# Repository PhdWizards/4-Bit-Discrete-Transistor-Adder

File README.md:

# 4-Bit Transistor Adder
A fully functional **4-bit binary adder** built using discrete transistor-resistor logic and standard 74HC-series logic ICs.
The project was developed from the initial logic design and transistor-level simulation to a custom two-layer PCB, PCB manufacturing, component assembly, and hardware testing.
The final circuit accepts two 4-bit binary numbers, adds them together, converts the resulting 5-bit value into decimal digits, and displays the result on two 7-segment displays.

## Overview
The main goal of this project was to design and build a physical digital calculator without relying on a microcontroller for the main arithmetic logic.
The core 4-bit adder was developed using **discrete transistor-resistor logic**.
The project includes:
- 4-bit binary addition
- Discrete transistor-based logic
- 5-bit binary result
- Binary-to-BCD conversion
- Two 7-segment displays
- CD4511 BCD-to-7-segment drivers
- Manual binary input using switches
- LED indicators for the binary result
- Custom two-layer PCB
- Complete KiCad schematic
- PCB design and Gerber manufacturing files
- Interactive Bill of Materials
- Falstad and Tinkercad simulations

## Specifications
| Parameter | Value |
|-----------|-------|
| Operation | 4-bit + 4-bit binary addition |
| Input A | 4 bits |
| Input B | 4 bits |
| Result | 5 bits |
| Result range | 0–30 |
| Supply voltage | 5 V |
| Power input | USB-C |
| PCB | 2-layer |
| PCB size | 166.37 × 181.61 mm |
| Main transistor | BC337-25 |
| Transistors | 100 |
| Resistors | 178 |
| 7-segment displays | 2 |
| BCD drivers | 2 × CD4511 |
| Binary input switches | 8 |
| LEDs | 6 |
| Microcontroller | None |

## How It Works

Two 4-bit binary values are entered using eight switches:
```text
A3 A2 A1 A0
B3 B2 B1 B0
```
The values are added together by the transistor-based logic, producing a 5-bit result:
```text
S4 S3 S2 S1 S0
```
The maximum possible result is:
```text
1111₂ + 1111₂ = 11110₂
```
which corresponds to:
```text
30₁₀
```
The 5-bit result is then converted into BCD:
```text
        5-bit Binary Result
                  │
                  ▼
          Binary-to-BCD
           Conversion
                  │
          ┌───────┴───────┐
          ▼               ▼
      Tens BCD         Ones BCD
          │               │
          ▼               ▼
       CD4511           CD4511
          │               │
          ▼               ▼
      7-Segment        7-Segment
       Display           Display
```
For example:
```text
10101₂ = 21₁₀
```
The two displays therefore show:
```text
21
```

## Hardware

### Final Board

## PCB Design

The PCB was designed in **KiCad** as a two-layer board.

### Front Side

### Back Side

### All Copper Layers

### 3D Model

## Schematic
The complete schematic was designed in KiCad and contains the transistor-based adder, logic ICs, BCD conversion, display drivers, inputs, indicators, and power circuitry.

A PDF version of the schematic is included in the `schematic` directory.
[**Open Schematic PDF**](schematic/sch.pdf)

## Bill of Materials

An **Interactive BOM** generated from KiCad is included in the repository.
It provides:
- Component references
- Component values
- Footprints
- Quantities
- Front and back PCB views
- Component locations
[**Open Interactive BOM**](bom/calculator-BOM.html)

## Simulation

Simulation was an important part of the development process.
Two different simulation environments were used for different stages of the project.

### Falstad
Falstad was used to learn and develop the transistor-based logic from the ground up.
The 4-bit adder was built step by step, starting from transistor-level digital logic and gradually combining the individual stages into a complete working 4-bit adder.
A downloadable Falstad simulation file is also included in the repository.
[**Open Simulation Documentation**](simulation/README.md)

### Tinkercad
Tinkercad was used to verify the digital logic and binary-to-BCD conversion.
The interactive Tinkercad simulation can be accessed through the simulation documentation.

## Development Process

The project was developed through the following stages:
```text
Concept
   ↓
Logic Design
   ↓
Transistor-Level Development
   ↓
Falstad Simulation
   ↓
Working 4-Bit Adder
   ↓
Tinkercad Simulation
   ↓
KiCad Schematic
   ↓
PCB Layout
   ↓
PCB Manufacturing
   ↓
Component Assembly
   ↓
Hardware Testing
```
The purpose of this workflow was to validate the logic progressively before moving to the final physical implementation.

## Manufacturing Files

The repository contains the files required to reproduce the PCB.
The `pcb` directory includes:
- KiCad PCB files
- Gerber manufacturing files
The schematic directory contains the KiCad schematic and PDF documentation.

## Repository Structure
```text
4-Bit-Transistor-Adder/
│
├── 📁 bom/
│   └── Interactive BOM
│
├── 📁 images/
│   ├── Project photos
│   ├── PCB renders
│   ├── PCB layers
│   ├── Schematic images
│   └── Simulation screenshots
│
├── 📁 pcb/
│   ├── KiCad PCB files
│   └── Gerber files
│
├── 📁 schematic/
│   ├── KiCad schematic
│   └── Schematic PDF
│
├── 📁 simulation/
│   ├── README.md
│   └── Falstad simulation file
│
└── README.md
```

# Tools Used
- **KiCad** — schematic and PCB design
- **Falstad Circuit Simulator** — transistor-level logic development
- **Tinkercad Circuits** — digital logic simulation

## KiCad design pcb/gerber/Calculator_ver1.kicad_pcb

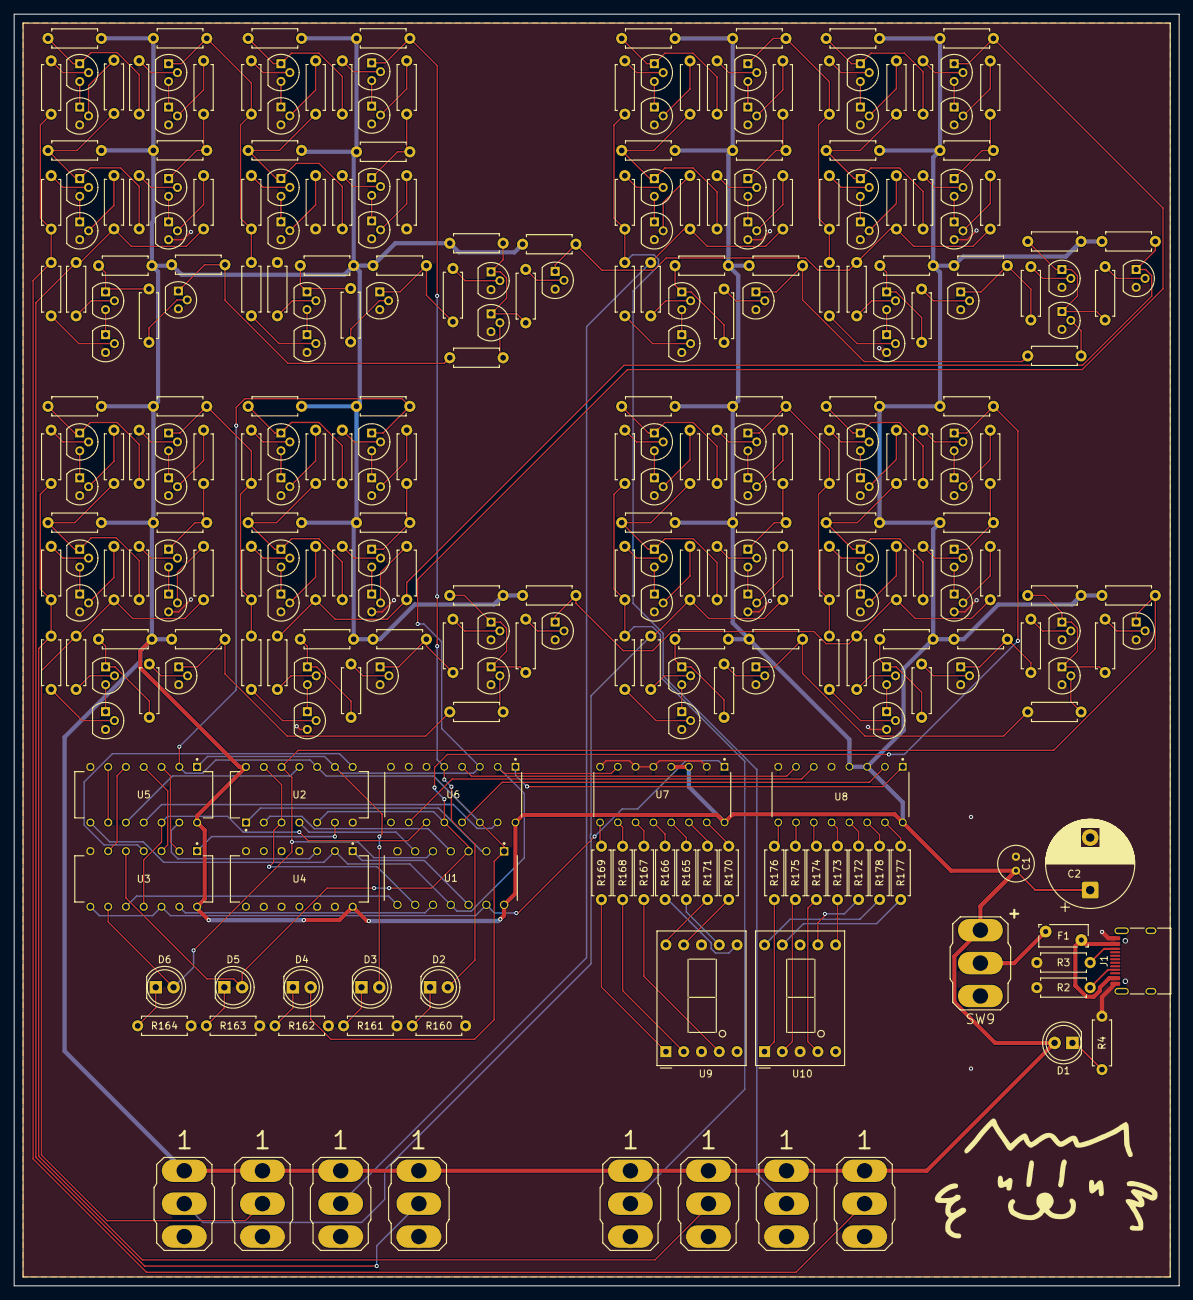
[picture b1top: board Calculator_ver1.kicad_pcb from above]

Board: 2 copper layers, 166.4 x 181.6 mm, 308 parts (0 on the bottom side), 267 nets.

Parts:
C1: 100nF; C_Radial_D5.0mm_H5.0mm_P2.00mm
C2: 100uF; CP_Radial_D12.5mm_P7.50mm
D1, D2, D3, D4, D5, D6: LED; LED_D5.0mm
F1: MF-R075; Fuse_Bourns_MF-RHT070
J1: USB_C_Receptacle_PowerOnly_24P; USB_C_Receptacle_HRO_TYPE-C-31-M-12
Q1, Q2, Q3, Q4, Q5, Q6, Q7, Q8, Q9, Q10, Q11, Q12, Q13, Q14, Q15, Q16, Q17, Q18, Q19, Q20, Q21, Q22, Q23, Q24, Q25, Q26, Q27, Q28, Q29, Q30, Q31, Q32, Q33, Q34, Q35, Q36, Q37, Q38, Q39, Q40, Q41, Q42, Q43, Q44, Q45, Q46, Q47, Q48, Q49, Q50, Q51, Q52, Q53, Q54, Q55, Q56, Q57, Q58, Q59, Q60, Q61, Q62, Q63, Q64, Q65, Q66, Q67, Q68, Q69, Q70, Q71, Q72, Q73, Q74, Q75, Q76, Q77, Q78, Q79, Q80, Q81, Q82, Q83, Q84, Q85, Q86, Q87, Q88, Q89, Q90, Q91, Q92, Q93, Q94, Q95, Q96, Q97, Q98, Q99, Q100: NPN; TO-92
R1, R5, R6, R7, R8, R9, R10, R11, R12, R13, R14, R15, R16, R17, R18, R19, R20, R21, R22, R23, R24, R25, R26, R27, R28, R29, R30, R31, R32, R33, R34, R35, R36, R37, R38, R39, R40, R41, R42, R43, R44, R45, R46, R47, R48, R49, R50, R51, R52, R53, R54, R55, R56, R57, R58, R59, R60, R61, R62, R63, R64, R65, R66, R67, R68, R69, R70, R71, R72, R73, R74, R75, R76, R77, R78, R79, R80, R81, R82, R83, R84, R85, R86, R87, R88, R89, R90, R91, R92, R93, R94, R95, R96, R97, R98, R99, R100, R101, R102, R103, R104, R105, R106, R107, R108, R109, R110, R111, R112, R113, R114, R115, R116, R117, R118, R119, R120, R121, R122, R123, R124, R125, R126, R127, R128, R129, R130, R131, R132, R133, R134, R135, R136, R137, R138, R139, R140, R141, R142, R143, R144, R145, R146, R147, R148, R149, R150, R151, R152, R153, R154, R155, R156, R157, R158, R159: 1k; R_Axial_DIN0207_L6.3mm_D2.5mm_P7.62mm_Horizontal
R2, R3: 5.1k; R_Axial_DIN0207_L6.3mm_D2.5mm_P7.62mm_Horizontal
R4, R160, R161, R162, R163, R164: 330R; R_Axial_DIN0207_L6.3mm_D2.5mm_P7.62mm_Horizontal
R165, R166, R167, R168, R169, R170, R171, R172, R173, R174, R175, R176, R177, R178: 330; R_Axial_DIN0207_L6.3mm_D2.5mm_P7.62mm_Horizontal
SW1, SW2, SW3, SW4, SW5, SW6, SW7, SW8, SW9: MTS-102
U1: 74HC04N; DIP764W47P254L1920H431Q14
U2, U3, U4: SN74HC08N; DIP794W45P254L1969H508Q14
U5: SN74HC32N; DIP794W45P254L1969H508Q14
U6: CD74HC283E; DIP794W45P254L1969H508Q16
U7, U8: CD4511BE; DIP794W45P254L1969H508Q16
U9, U10: D148K; D1X8K
g: LOGO; logocat

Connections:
+5V: C1.1, C2.1, D1.2 (A), R5.2, R9.2, R12.2, R15.2, R18.2, R20.2, R23.2, R30.2, R31.2, R32.2, R36.2, R37.2, R39.2, R42.2, R45.2, R52.2, R53.2, R54.2, R58.2, R59.2, R62.2, R69.2, R70.2, R71.2, R77.2, R78.2, R79.2, R81.2, R84.2, R91.2, R92.2, R93.2, R97.2, R98.2, R101.2, R108.2, R109.2, R110.2, R116.2, R117.2, R118.2, R120.2, R123.2, R130.2, R131.2, R132.2, R136.2, R137.2, R140.2, R147.2, R148.2, R149.2, R155.2, R156.2, R157.2, R159.2, SW1.1 (A), SW2.1 (A), SW3.1 (A), SW4.1 (A), SW5.1 (A), SW6.1 (A), SW7.1 (A), SW8.1 (A), SW9.1 (A), U1.14 (VCC), U2.14 (VCC), U3.14 (VCC), U4.14 (VCC), U5.14 (VCC), U6.16 (VCC), U7.3 (~LT), U7.4 (~BL), U7.16 (VDD), U8.3 (~LT), U8.4 (~BL), U8.16 (VDD)
/A0: R1.1, R7.1, R17.1, SW1.2 (B)
/A1: R43.1, R46.1, R51.1, SW2.2 (B)
/A1I: U1.8 (4Y), U3.10 (3B)
/A2: R82.1, R85.1, R90.1, SW3.2 (B)
/A3: R121.1, R124.1, R129.1, SW4.2 (B)
/A11: U1.9 (4A), U2.3 (1Y), U2.13 (4B)
/A22: U2.6 (2Y), U3.1 (1A)
/A33: U2.8 (3Y), U3.4 (2A)
/A44: U2.11 (4Y), U5.10 (3B)
/B0: R6.1, R11.1, R16.1, SW5.2 (B)
/B1: R44.1, R49.1, R50.1, SW6.2 (B)
/B2: R83.1, R88.1, R89.1, SW7.2 (B)
/B3: R122.1, R127.1, R128.1, SW8.2 (B)
/B3I: U1.12 (6Y), U4.1 (1A)
/B11: U3.3 (1Y), U5.4 (2A)
/B22: U3.6 (2Y), U5.5 (2B)
/B33: U1.13 (6A), U3.8 (3Y), U3.12 (4A), U7.1 (B_IN)
/B44: U3.11 (4Y), U5.12 (4A), U6.11 (B3)
/C1: U4.3 (1Y), U5.13 (4B)
/Cout1: Q25.1 (C), R42.1, R61.1, R66.1, R67.1
/Cout2: Q50.1 (C), R81.1, R100.1, R105.1, R106.1
/Cout3: Q75.1 (C), R120.1, R139.1, R144.1, R145.1
/Cout4: D6.2 (A), Q100.1 (C), R159.1, U1.5 (3A), U2.12 (4A), U3.9 (3A)
/Cout4I: U1.6 (3Y), U2.4 (2A)
/D1: U3.2 (1B), U5.3 (1Y)
/D2: U5.6 (2Y), U5.9 (3A)
/D3: U1.11 (5A), U4.2 (1B), U5.8 (3Y), U6.2 (B1), U7.7 (A_IN)
/D3I: U1.10 (5Y), U3.13 (4B)
/D4: U5.11 (4Y), U6.15 (B2)
/S0: U6.4 (S0), U8.7 (A_IN)
/S1: U6.1 (S1), U8.1 (B_IN)
/S2: U6.13 (S2), U8.2 (C_IN)
/S3: U6.10 (S3), U8.6 (D_IN)
/Sum1: D2.2 (A), Q21.1 (C), R37.1, U6.5 (A0)
/Sum2: D3.2 (A), Q48.1 (C), R79.1, U2.9 (3A), U5.1 (1A), U6.3 (A1)
/Sum3: D4.2 (A), Q73.1 (C), R118.1, U1.1 (1A), U2.10 (3B), U5.2 (1B), U6.14 (A2)
/Sum3I: U1.2 (1Y), U2.1 (1A)
/Sum4: D5.2 (A), Q98.1 (C), R157.1, U1.3 (2A), U2.5 (2B), U3.5 (2B), U6.12 (A3)
/Sum4I: U1.4 (2Y), U2.2 (1B)
/VBUS: F1.1, J1.A4 (VBUS), J1.A9 (VBUS), J1.B4 (VBUS), J1.B9 (VBUS)
GND: C1.2, C2.2, J1.A1 (GND), J1.A12 (GND), J1.B1 (GND), J1.B12 (GND), Q2.3 (E), Q4.3 (E), Q6.3 (E), Q8.3 (E), Q10.3 (E), Q11.3 (E), Q13.3 (E), Q15.3 (E), Q17.3 (E), Q19.3 (E), Q20.3 (E), Q22.3 (E), Q23.3 (E), Q24.3 (E), Q25.3 (E), Q27.3 (E), Q29.3 (E), Q31.3 (E), Q33.3 (E), Q34.3 (E), Q36.3 (E), Q38.3 (E), Q40.3 (E), Q42.3 (E), Q44.3 (E), Q45.3 (E), Q46.3 (E), Q47.3 (E), Q49.3 (E), Q50.3 (E), Q52.3 (E), Q54.3 (E), Q56.3 (E), Q58.3 (E), Q59.3 (E), Q61.3 (E), Q63.3 (E), Q65.3 (E), Q67.3 (E), Q69.3 (E), Q70.3 (E), Q71.3 (E), Q72.3 (E), Q74.3 (E), Q75.3 (E), Q77.3 (E), Q79.3 (E), Q81.3 (E), Q83.3 (E), Q84.3 (E), Q86.3 (E), Q88.3 (E), Q90.3 (E), Q92.3 (E), Q94.3 (E), Q95.3 (E), Q96.3 (E), Q97.3 (E), Q99.3 (E), Q100.3 (E), R2.2, R3.2, R4.2, R22.1, R27.1, R28.1, R160.2, R161.2, R162.2, R163.2, R164.2, SW1.3 (C), SW2.3 (C), SW3.3 (C), SW4.3 (C), SW5.3 (C), SW6.3 (C), SW7.3 (C), SW8.3 (C), U1.7 (GND), U2.7 (GND), U3.7 (GND), U4.4 (2A), U4.5 (2B), U4.7 (GND), U4.9 (3A), U4.10 (3B), U4.12 (4A), U4.13 (4B), U5.7 (GND), U6.6 (B0), U6.7 (CIN), U6.8 (GND), U7.2 (C_IN), U7.5 (LE/~STROBE), U7.6 (D_IN), U7.8 (VSS), U8.5 (LE/~STROBE), U8.8 (VSS), U9.3 (CC), U9.8 (CC), U10.3 (CC), U10.8 (CC)
unnamed: D1.1 (K), R4.1
unnamed: D2.1 (K), R160.1
unnamed: D3.1 (K), R161.1
unnamed: D4.1 (K), R162.1
unnamed: D5.1 (K), R163.1
unnamed: D6.1 (K), R164.1
unnamed: J1.A5 (CC1), R2.1
unnamed: J1.B5 (CC2), R3.1
unnamed: Q1.2 (B), R1.2
unnamed: Q1.1 (C), R5.1, R8.1, R10.1
unnamed: Q1.3 (E), Q2.1 (C)
unnamed: Q2.2 (B), R6.2
unnamed: Q3.2 (B), R7.2
unnamed: Q3.1 (C), R9.1, R13.1
unnamed: Q3.3 (E), Q4.1 (C)
unnamed: Q4.2 (B), R8.2
unnamed: Q5.2 (B), R10.2
unnamed: Q5.1 (C), R12.1, R14.1
unnamed: Q5.3 (E), Q6.1 (C)
unnamed: Q6.2 (B), R11.2
unnamed: Q7.2 (B), R13.2
unnamed: Q7.1 (C), R15.1, R21.1, R24.1, R29.1
unnamed: Q7.3 (E), Q8.1 (C)
unnamed: Q8.2 (B), R14.2
unnamed: Q9.2 (B), R16.2
unnamed: Q9.1 (C), R18.1, R19.1
unnamed: Q10.2 (B), R17.2
unnamed: Q9.3 (E), Q10.1 (C)
unnamed: Q11.2 (B), R19.2
unnamed: Q11.1 (C), R20.1, R40.1
unnamed: Q12.2 (B), R21.2
unnamed: Q12.1 (C), R23.1, R25.1, R26.1
unnamed: Q12.3 (E), Q13.1 (C)
unnamed: Q13.2 (B), R22.2
unnamed: Q14.2 (B), R24.2
unnamed: Q14.1 (C), R30.1, R34.1
unnamed: Q14.3 (E), Q15.1 (C)
unnamed: Q15.2 (B), R25.2
unnamed: Q16.2 (B), R26.2
unnamed: Q16.1 (C), R31.1, R35.1
unnamed: Q16.3 (E), Q17.1 (C)
unnamed: Q17.2 (B), R27.2
unnamed: Q18.2 (B), R28.2
unnamed: Q18.1 (C), R32.1, R33.1
unnamed: Q18.3 (E), Q19.1 (C)
unnamed: Q19.2 (B), R29.2
unnamed: Q20.2 (B), R33.2
unnamed: Q20.1 (C), R36.1, R38.1
unnamed: Q21.2 (B), R34.2
unnamed: Q21.3 (E), Q22.1 (C)
unnamed: Q22.2 (B), R35.2
unnamed: Q23.2 (B), R38.2
unnamed: Q23.1 (C), Q24.1 (C), R39.1, R41.1
unnamed: Q24.2 (B), R40.2
unnamed: Q25.2 (B), R41.2
unnamed: Q26.2 (B), R43.2
unnamed: Q26.1 (C), R45.1, R47.1, R48.1
unnamed: Q26.3 (E), Q27.1 (C)
unnamed: Q27.2 (B), R44.2
unnamed: Q28.2 (B), R46.2
unnamed: Q28.1 (C), R52.1, R56.1
unnamed: Q28.3 (E), Q29.1 (C)
unnamed: Q29.2 (B), R47.2
unnamed: Q30.2 (B), R48.2
unnamed: Q30.1 (C), R53.1, R57.1
unnamed: Q30.3 (E), Q31.1 (C)
unnamed: Q31.2 (B), R49.2
unnamed: Q32.2 (B), R50.2
unnamed: Q32.1 (C), R54.1, R55.1
unnamed: Q32.3 (E), Q33.1 (C)
unnamed: Q33.2 (B), R51.2
unnamed: Q34.2 (B), R55.2
unnamed: Q34.1 (C), R58.1, R74.1
unnamed: Q35.2 (B), R56.2
unnamed: Q35.1 (C), R59.1, R60.1, R63.1, R68.1
unnamed: Q35.3 (E), Q36.1 (C)
unnamed: Q36.2 (B), R57.2
unnamed: Q37.2 (B), R60.2
unnamed: Q37.1 (C), R62.1, R64.1, R65.1
unnamed: Q37.3 (E), Q38.1 (C)
unnamed: Q38.2 (B), R61.2
unnamed: Q39.2 (B), R63.2
unnamed: Q39.1 (C), R69.1, R75.1
unnamed: Q39.3 (E), Q40.1 (C)
unnamed: Q40.2 (B), R64.2
unnamed: Q41.2 (B), R65.2
unnamed: Q41.1 (C), R70.1, R76.1
unnamed: Q41.3 (E), Q42.1 (C)
unnamed: Q42.2 (B), R66.2
unnamed: Q43.2 (B), R67.2
unnamed: Q43.1 (C), R71.1, R72.1
unnamed: Q43.3 (E), Q44.1 (C)
unnamed: Q44.2 (B), R68.2
unnamed: Q45.2 (B), R72.2
unnamed: Q45.1 (C), R73.1, R77.1
unnamed: Q46.2 (B), R73.2
unnamed: Q46.1 (C), Q47.1 (C), R78.1, R80.1
unnamed: Q47.2 (B), R74.2
unnamed: Q48.2 (B), R75.2
unnamed: Q48.3 (E), Q49.1 (C)
unnamed: Q49.2 (B), R76.2
unnamed: Q50.2 (B), R80.2
unnamed: Q51.2 (B), R82.2
unnamed: Q51.1 (C), R84.1, R86.1, R87.1
unnamed: Q51.3 (E), Q52.1 (C)
unnamed: Q52.2 (B), R83.2
unnamed: Q53.2 (B), R85.2
unnamed: Q53.1 (C), R91.1, R95.1
unnamed: Q53.3 (E), Q54.1 (C)
unnamed: Q54.2 (B), R86.2
unnamed: Q55.2 (B), R87.2
unnamed: Q55.1 (C), R92.1, R96.1
unnamed: Q55.3 (E), Q56.1 (C)
unnamed: Q56.2 (B), R88.2
unnamed: Q57.2 (B), R89.2
unnamed: Q57.1 (C), R93.1, R94.1
unnamed: Q57.3 (E), Q58.1 (C)
unnamed: Q58.2 (B), R90.2
unnamed: Q59.2 (B), R94.2
unnamed: Q59.1 (C), R97.1, R113.1
unnamed: Q60.2 (B), R95.2
unnamed: Q60.1 (C), R98.1, R99.1, R102.1, R107.1
unnamed: Q60.3 (E), Q61.1 (C)
unnamed: Q61.2 (B), R96.2
unnamed: Q62.2 (B), R99.2
unnamed: Q62.1 (C), R101.1, R103.1, R104.1
unnamed: Q62.3 (E), Q63.1 (C)
unnamed: Q63.2 (B), R100.2
unnamed: Q64.2 (B), R102.2
unnamed: Q64.1 (C), R108.1, R114.1
unnamed: Q64.3 (E), Q65.1 (C)
unnamed: Q65.2 (B), R103.2
unnamed: Q66.2 (B), R104.2
unnamed: Q66.1 (C), R109.1, R115.1
unnamed: Q66.3 (E), Q67.1 (C)
unnamed: Q67.2 (B), R105.2
unnamed: Q68.2 (B), R106.2
unnamed: Q68.1 (C), R110.1, R111.1
unnamed: Q68.3 (E), Q69.1 (C)
unnamed: Q69.2 (B), R107.2
unnamed: Q70.2 (B), R111.2
unnamed: Q70.1 (C), R112.1, R116.1
unnamed: Q71.2 (B), R112.2
unnamed: Q71.1 (C), Q72.1 (C), R117.1, R119.1
unnamed: Q72.2 (B), R113.2
unnamed: Q73.2 (B), R114.2
unnamed: Q73.3 (E), Q74.1 (C)
unnamed: Q74.2 (B), R115.2
unnamed: Q75.2 (B), R119.2
unnamed: Q76.2 (B), R121.2
unnamed: Q76.1 (C), R123.1, R125.1, R126.1
unnamed: Q76.3 (E), Q77.1 (C)
unnamed: Q77.2 (B), R122.2
unnamed: Q78.2 (B), R124.2
unnamed: Q78.1 (C), R130.1, R134.1
unnamed: Q78.3 (E), Q79.1 (C)
unnamed: Q79.2 (B), R125.2
unnamed: Q80.2 (B), R126.2
unnamed: Q80.1 (C), R131.1, R135.1
unnamed: Q80.3 (E), Q81.1 (C)
unnamed: Q81.2 (B), R127.2
unnamed: Q82.2 (B), R128.2
unnamed: Q82.1 (C), R132.1, R133.1
unnamed: Q82.3 (E), Q83.1 (C)
unnamed: Q83.2 (B), R129.2
unnamed: Q84.2 (B), R133.2
unnamed: Q84.1 (C), R136.1, R152.1
unnamed: Q85.2 (B), R134.2
unnamed: Q85.1 (C), R137.1, R138.1, R141.1, R146.1
unnamed: Q85.3 (E), Q86.1 (C)
unnamed: Q86.2 (B), R135.2
unnamed: Q87.2 (B), R138.2
unnamed: Q87.1 (C), R140.1, R142.1, R143.1
unnamed: Q87.3 (E), Q88.1 (C)
unnamed: Q88.2 (B), R139.2
unnamed: Q89.2 (B), R141.2
unnamed: Q89.1 (C), R147.1, R153.1
unnamed: Q89.3 (E), Q90.1 (C)
unnamed: Q90.2 (B), R142.2
unnamed: Q91.2 (B), R143.2
unnamed: Q91.1 (C), R148.1, R154.1
unnamed: Q91.3 (E), Q92.1 (C)
unnamed: Q92.2 (B), R144.2
unnamed: Q93.2 (B), R145.2
unnamed: Q93.1 (C), R149.1, R150.1
unnamed: Q93.3 (E), Q94.1 (C)
unnamed: Q94.2 (B), R146.2
unnamed: Q95.2 (B), R150.2
unnamed: Q95.1 (C), R151.1, R155.1
unnamed: Q96.2 (B), R151.2
unnamed: Q96.1 (C), Q97.1 (C), R156.1, R158.1
unnamed: Q97.2 (B), R152.2
unnamed: Q98.2 (B), R153.2
unnamed: Q98.3 (E), Q99.1 (C)
unnamed: Q99.2 (B), R154.2
unnamed: Q100.2 (B), R158.2
unnamed: F1.2, SW9.2 (B)
unnamed: R165.2, U7.13 (A_OUT)
unnamed: R166.2, U7.12 (B_OUT)
unnamed: R167.2, U7.11 (C_OUT)
unnamed: R168.2, U7.10 (D_OUT)
unnamed: R169.2, U7.9 (E_OUT)
unnamed: R170.2, U7.15 (F_OUT)
unnamed: R171.2, U7.14 (G_OUT)
unnamed: R172.2, U8.13 (A_OUT)
unnamed: R173.2, U8.12 (B_OUT)
unnamed: R174.2, U8.11 (C_OUT)
unnamed: R175.2, U8.10 (D_OUT)
unnamed: R176.2, U8.9 (E_OUT)
unnamed: R177.2, U8.15 (F_OUT)
unnamed: R178.2, U8.14 (G_OUT)
unnamed: R165.1, U9.7 (A)
unnamed: R166.1, U9.6 (B)
unnamed: R167.1, U9.4 (C)
unnamed: R168.1, U9.2 (D)
unnamed: R169.1, U9.1 (E)
unnamed: R170.1, U9.9 (F)
unnamed: R171.1, U9.10 (G)
unnamed: R172.1, U10.7 (A)
unnamed: R173.1, U10.6 (B)
unnamed: R174.1, U10.4 (C)
unnamed: R175.1, U10.2 (D)
unnamed: R176.1, U10.1 (E)
unnamed: R177.1, U10.9 (F)
unnamed: R178.1, U10.10 (G)
